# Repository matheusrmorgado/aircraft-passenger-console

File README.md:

# Controles Acessíveis em Aeronaves

## Projeto

Projeto desenvolvido em parceria com o [InovaLab@Poli](https://www.facebook.com/INOVALAB.POLI) e o [Centro Interdisciplinar de Tecnologias Interativas (CITI-USP)](http://www.lsi.usp.br/citi/).

O relatório completo do trabalho está disponível em [final-report.pdf](https://github.com/matheusrmorgado/aircraft-passenger-console/blob/master/final-report.pdf).

Uma apresentação resumida do projeto e dos resultados está disponível em [poster-presentation.pdf](https://github.com/matheusrmorgado/aircraft-passenger-console/blob/master/poster-presentation.pdf).

<p align="center">
  <i> Youtube Video - https://youtu.be/7tW5oUx-QU8</i>
</p>

## Apresentação em Eventos

### Campus Mobile 2016 (Air Assistant)

> https://www.institutonetclaroembratel.org.br/educacao/nossas-novidades/noticias/jovens-empreendedores-se-reunem-na-etapa-presencial-do-programa-campus-mobile/

### IEEE ISCE 2016 (Enabling Technologies)

> http://isce2016.org.br/#overview_and_technical_program 

### TOM 2016  (Projetos 2016 - Slide 29)

> http://tom-sp.sedpcd.sp.gov.br/img/TOM.pdf

## Participação em Reportagens

### Movimento Maker - Estadão

> http://infograficos.estadao.com.br/e/focas/movimento-maker/tem-maker-na-medicina.php

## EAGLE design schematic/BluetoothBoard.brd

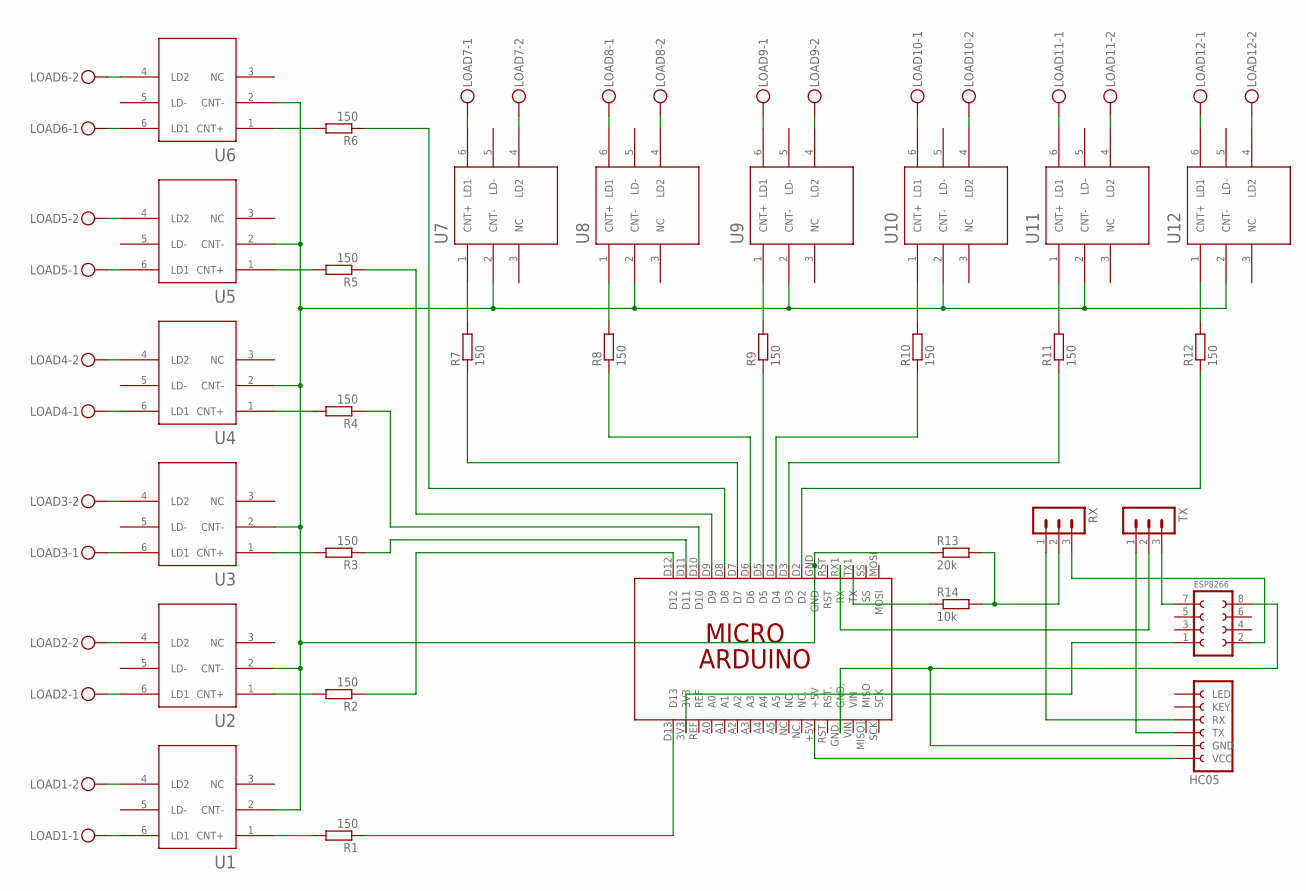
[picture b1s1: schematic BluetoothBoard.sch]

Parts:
ESP8266: ESP8266
HC05: FE06-1; FE06
LOAD1, LOAD2, LOAD3, LOAD4, LOAD5, LOAD6, LOAD7, LOAD8, LOAD9, LOAD10, LOAD11, LOAD12: MKDSN1,5/2-5,08
R1, R2, R3, R4, R5, R6, R7, R8, R9, R10, R11, R12: 150; 0207/7
R13: 20k; 0207/7
R14: 10k; 0207/7
RX: MA03-1
TX: MA03-1
U1, U2, U3, U4, U5, U6, U7, U8, U9, U10, U11, U12: LCA710; DIL-06
UC: ARDUINO_MICRO

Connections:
GND: R13.1, U1.2 (CNT-), U2.2 (CNT-), U3.2 (CNT-), U4.2 (CNT-), U5.2 (CNT-), U6.2 (CNT-), U7.2 (CNT-), U8.2 (CNT-), U9.2 (CNT-), U10.2 (CNT-), U11.2 (CNT-), U12.2 (CNT-), UC.GND
unnamed: R1.2, U1.1 (CNT+)
unnamed: LOAD1.2, U1.4 (LD2)
unnamed: LOAD1.1, U1.6 (LD1)
unnamed: R2.2, U2.1 (CNT+)
unnamed: LOAD2.1, U2.6 (LD1)
unnamed: LOAD2.2, U2.4 (LD2)
unnamed: R3.2, U3.1 (CNT+)
unnamed: LOAD3.1, U3.6 (LD1)
unnamed: LOAD3.2, U3.4 (LD2)
unnamed: R4.2, U4.1 (CNT+)
unnamed: LOAD4.1, U4.6 (LD1)
unnamed: LOAD4.2, U4.4 (LD2)
unnamed: R5.2, U5.1 (CNT+)
unnamed: LOAD5.1, U5.6 (LD1)
unnamed: LOAD5.2, U5.4 (LD2)
unnamed: R6.2, U6.1 (CNT+)
unnamed: LOAD6.1, U6.6 (LD1)
unnamed: LOAD6.2, U6.4 (LD2)
unnamed: TX.2, UC.RX1 (RX)
unnamed: ESP8266.1, UC.3V3
unnamed: R14.1, UC.TX1 (TX)
unnamed: ESP8266.2, RX.3
unnamed: R7.2, U7.1 (CNT+)
unnamed: LOAD7.1, U7.6 (LD1)
unnamed: LOAD7.2, U7.4 (LD2)
unnamed: R13.2, R14.2, RX.2
unnamed: R8.2, U8.1 (CNT+)
unnamed: LOAD8.1, U8.6 (LD1)
unnamed: HC05.6 (VCC), UC.+5V
unnamed: HC05.3 (RX), RX.1
unnamed: LOAD8.2, U8.4 (LD2)
unnamed: ESP8266.7 (TX), TX.3
unnamed: HC05.4 (TX), TX.1
unnamed: R9.2, U9.1 (CNT+)
unnamed: LOAD9.1, U9.6 (LD1)
unnamed: LOAD9.2, U9.4 (LD2)
unnamed: R10.2, U10.1 (CNT+)
unnamed: LOAD10.1, U10.6 (LD1)
unnamed: LOAD10.2, U10.4 (LD2)
unnamed: R11.2, U11.1 (CNT+)
unnamed: LOAD11.1, U11.6 (LD1)
unnamed: LOAD11.2, U11.4 (LD2)
unnamed: R12.2, U12.1 (CNT+)
unnamed: LOAD12.1, U12.6 (LD1)
unnamed: LOAD12.2, U12.4 (LD2)
unnamed: ESP8266.8, HC05.5 (GND), UC.GND.
unnamed: R12.1, UC.D2
unnamed: R11.1, UC.D3
unnamed: R10.1, UC.D4
unnamed: R9.1, UC.D5
unnamed: R8.1, UC.D6
unnamed: R7.1, UC.D7
unnamed: R6.1, UC.D8
unnamed: R5.1, UC.D9
unnamed: R4.1, UC.D10
unnamed: R3.1, UC.D11
unnamed: R1.1, UC.D13
unnamed: R2.1, UC.D12

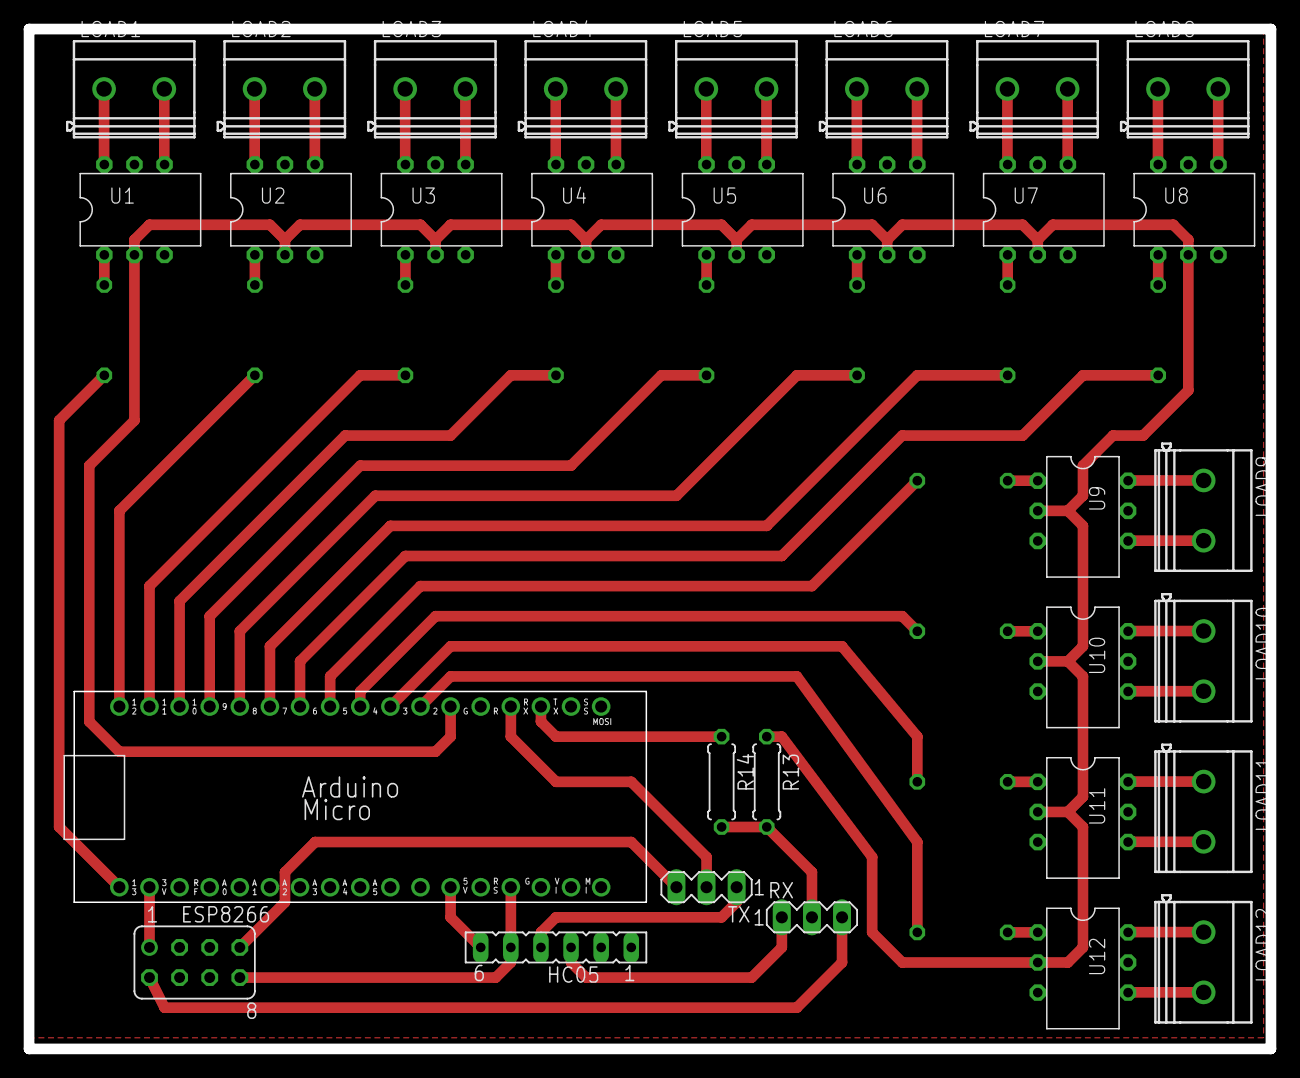
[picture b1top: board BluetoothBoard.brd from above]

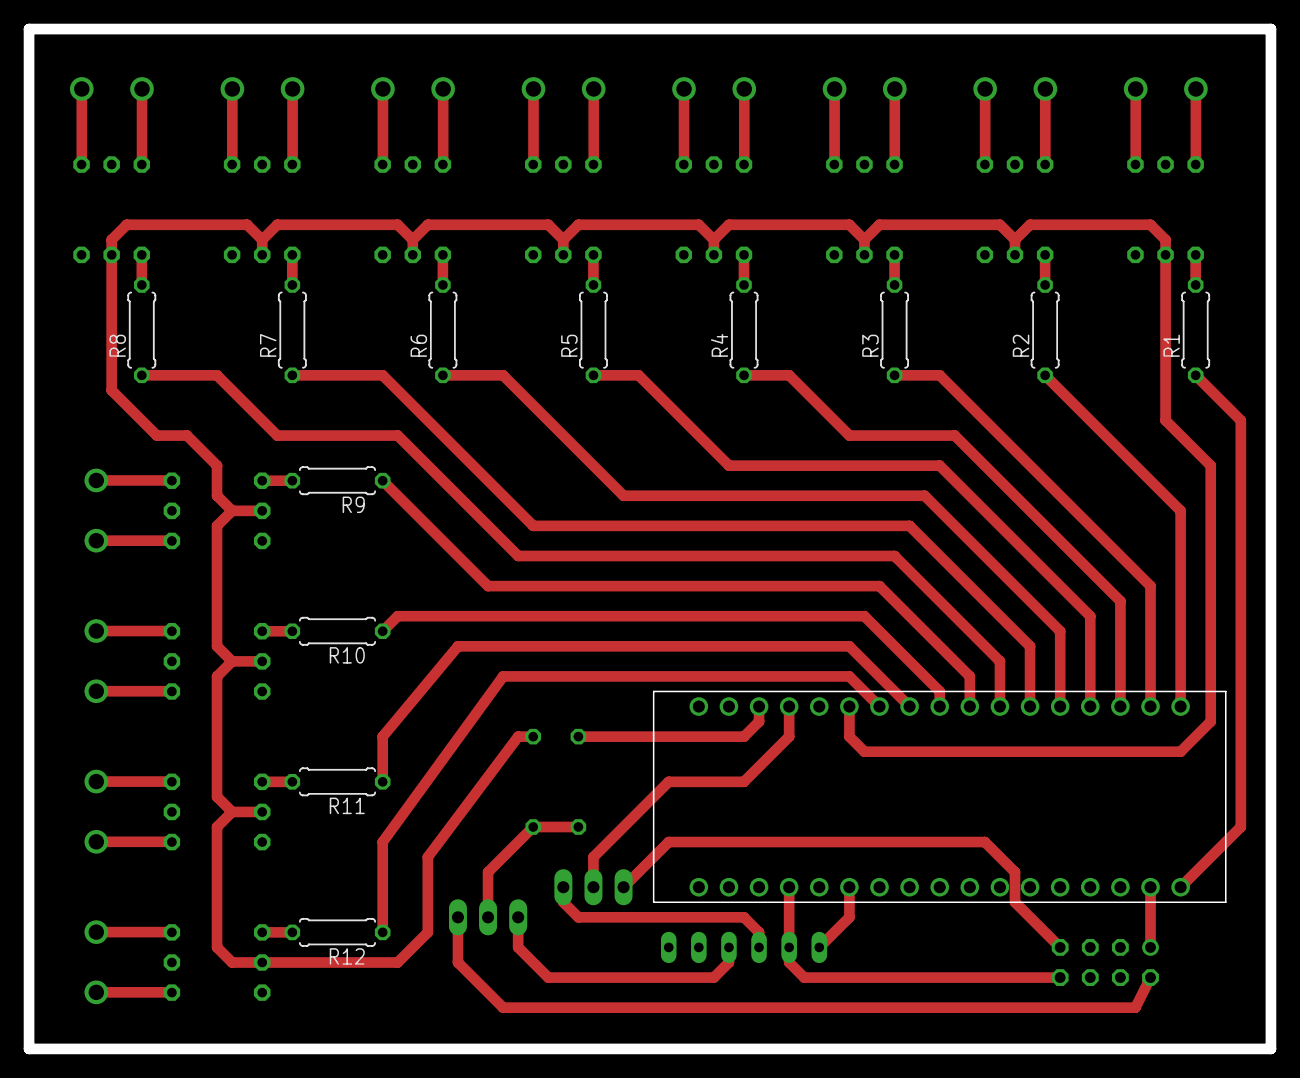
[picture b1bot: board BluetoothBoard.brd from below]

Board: 2 copper layers, 104.8 x 86.0 mm, 43 parts (12 on the bottom side), 59 nets.

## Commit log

2017-12-31 Add files to repository
2018-01-27 Update license information
2019-03-31 Update project documentation
2019-03-31 Update schematic files
2023-05-23 Criado usando o Colaboratory
